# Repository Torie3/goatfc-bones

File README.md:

# 🐐 GoatFC-Bones - Open Source FPV Flight Controller

<div align="left">
  <p>
    <strong>GoatFC-Bones</strong> is a compact, cheap, open-source FPV drone flight controller designed for racing builds without sacrificing performance. It’s ideal for hobbyists who want simple hardware so that they can easily understand what is happening in their quadcopter.
  </p>
</div>

## 🔧 Key Features

- **Voltage Regulation:**
  - 5V and 12V BEC outputs
  - Dual 3.3V LDOs:
    - One dedicated to the IMU for **noise isolation**
    - One for the rest of the system

- **Connectivity:**
  - Micro-USB for configuration
  - 20x20mm standard mounting pattern
  - ESC connector for clean wiring
  - 6-pin HD video system plug

- **Software:**
  - Compatible with [Betaflight](https://betaflight.com/) no official target yet!

- **License & Use:**
  - **Open-source** – build it, modify it, improve it
  - **Non-commercial** – redistribution for sale is **not allowed**
## 🧷 Pinout Diagram

Below is the pinout for the GoatFC-Bones flight controller. Make sure to reference this schematic when wiring your components.

> ⚠️ **Note:** The dedicated 3.3V regulators *are* broken out on the board, but **they are not intended for external use**. If you're curious about their exact location or implementation, please refer to the KiCad design files. Avoid connecting anything to these lines unless you fully understand the design — using them improperly may cause instability or damage.

> 🔌 Always double-check with a multimeter before connecting components!
## 🛠️ Building Your Own GoatFC-Bones

Amazing that you want to build one!

You can order the PCBs from your favorite PCB manufacturer — the Gerber files are available in the folder:  
[Gerber Files Folder](./gerber%20files)

### 📦 Bill of Materials (BOM)

The BOM is provided as an **interactive BOM**, which you can view here:  
[Download and open html file here](./interactive-bom)

The iBOM makes it easy to locate and identify all the required components. Just search for the parts and order them from your preferred distributor.

### 🔧 Assembly Tips

- Solder all components following the iBOM placement guide
- Use **solder paste** and a **hot air station** for best results
- All components are **0402 size** — small, but manageable with some patience
- If you're new to SMD soldering, it's a good idea to practice on a scrap board first!

Good luck, and enjoy flying with your custom GoatFC-Bones FC!

## Flashing Betaflight to GoatFC-Bones

Follow these steps to flash Betaflight firmware to your GoatFC-Bones flight controller:

### Requirements
- A fully assembled GoatFC-Bones FC
- [Betaflight Configurator](https://github.com/betaflight/betaflight-configurator/releases) (latest version) installed on your PC

### Flashing Steps

1. **Build and assemble** your GoatFC-Bones FC.
2. **Install the latest Betaflight Configurator** on your computer.
3. **Enter DFU mode**:
   - Hold down the **boot button** on the FC while plugging in the **Micro-USB** cable.
4. In Betaflight Configurator, your FC should now show up as **DFU Bootloader**.
5. Go to the **Firmware Flasher** tab.
6. Under **Board**, select:  
   **`FOXEERF722V4`** (GoatFC-Bones shares a pinout with the Foxeer Mini V4).
7. Choose your preferred **firmware version** from the dropdown.
8. Click **Load Firmware [Online]**.
9. Then click **Flash Firmware**.
10. Once flashing is complete, the firmware is installed and ready to go! 🎉

### ⚠️ Important: Motor Remapping Required

Because the motor layout on GoatFC-Bones differs from the Foxeer Mini V4, you must **remap the motors** in the CLI:

1. Go to the **CLI** tab
2. In the cli type:
```
resource MOTOR 1 PC08
resource MOTOR 2 PC09
resource MOTOR 3 PA08
resource MOTOR 4 PA09
save
```
4. Now your motors should be in the correct order.
- You only need to do this once — after that, you can **save your configuration as a preset** to reload easily next time.

> 💡 Tip: After remapping, test motor directions in the “Motors” tab and double-check the order before your first flight.

---

## ⚠️ Disclaimer

This project is provided **as-is** without any warranty or guarantee of functionality or safety.

By using the GoatFC-Bones design files, firmware configurations, or build instructions, you acknowledge and agree that:

- You are solely responsible for your own safety and the safety of others.
- You assume all risks associated with the assembly, flashing, and use of this hardware.
- I (the creator) am **not liable** for any damage, injury, loss, or malfunction resulting from the use, misuse, or failure of this project.
- Always follow proper electrical and flight safety practices, and ensure compliance with your local laws and regulations.

> 🚧 Use at your own risk. This is an open-source DIY project intended for educational and recreational purposes (drone racing an amazing hobby!).

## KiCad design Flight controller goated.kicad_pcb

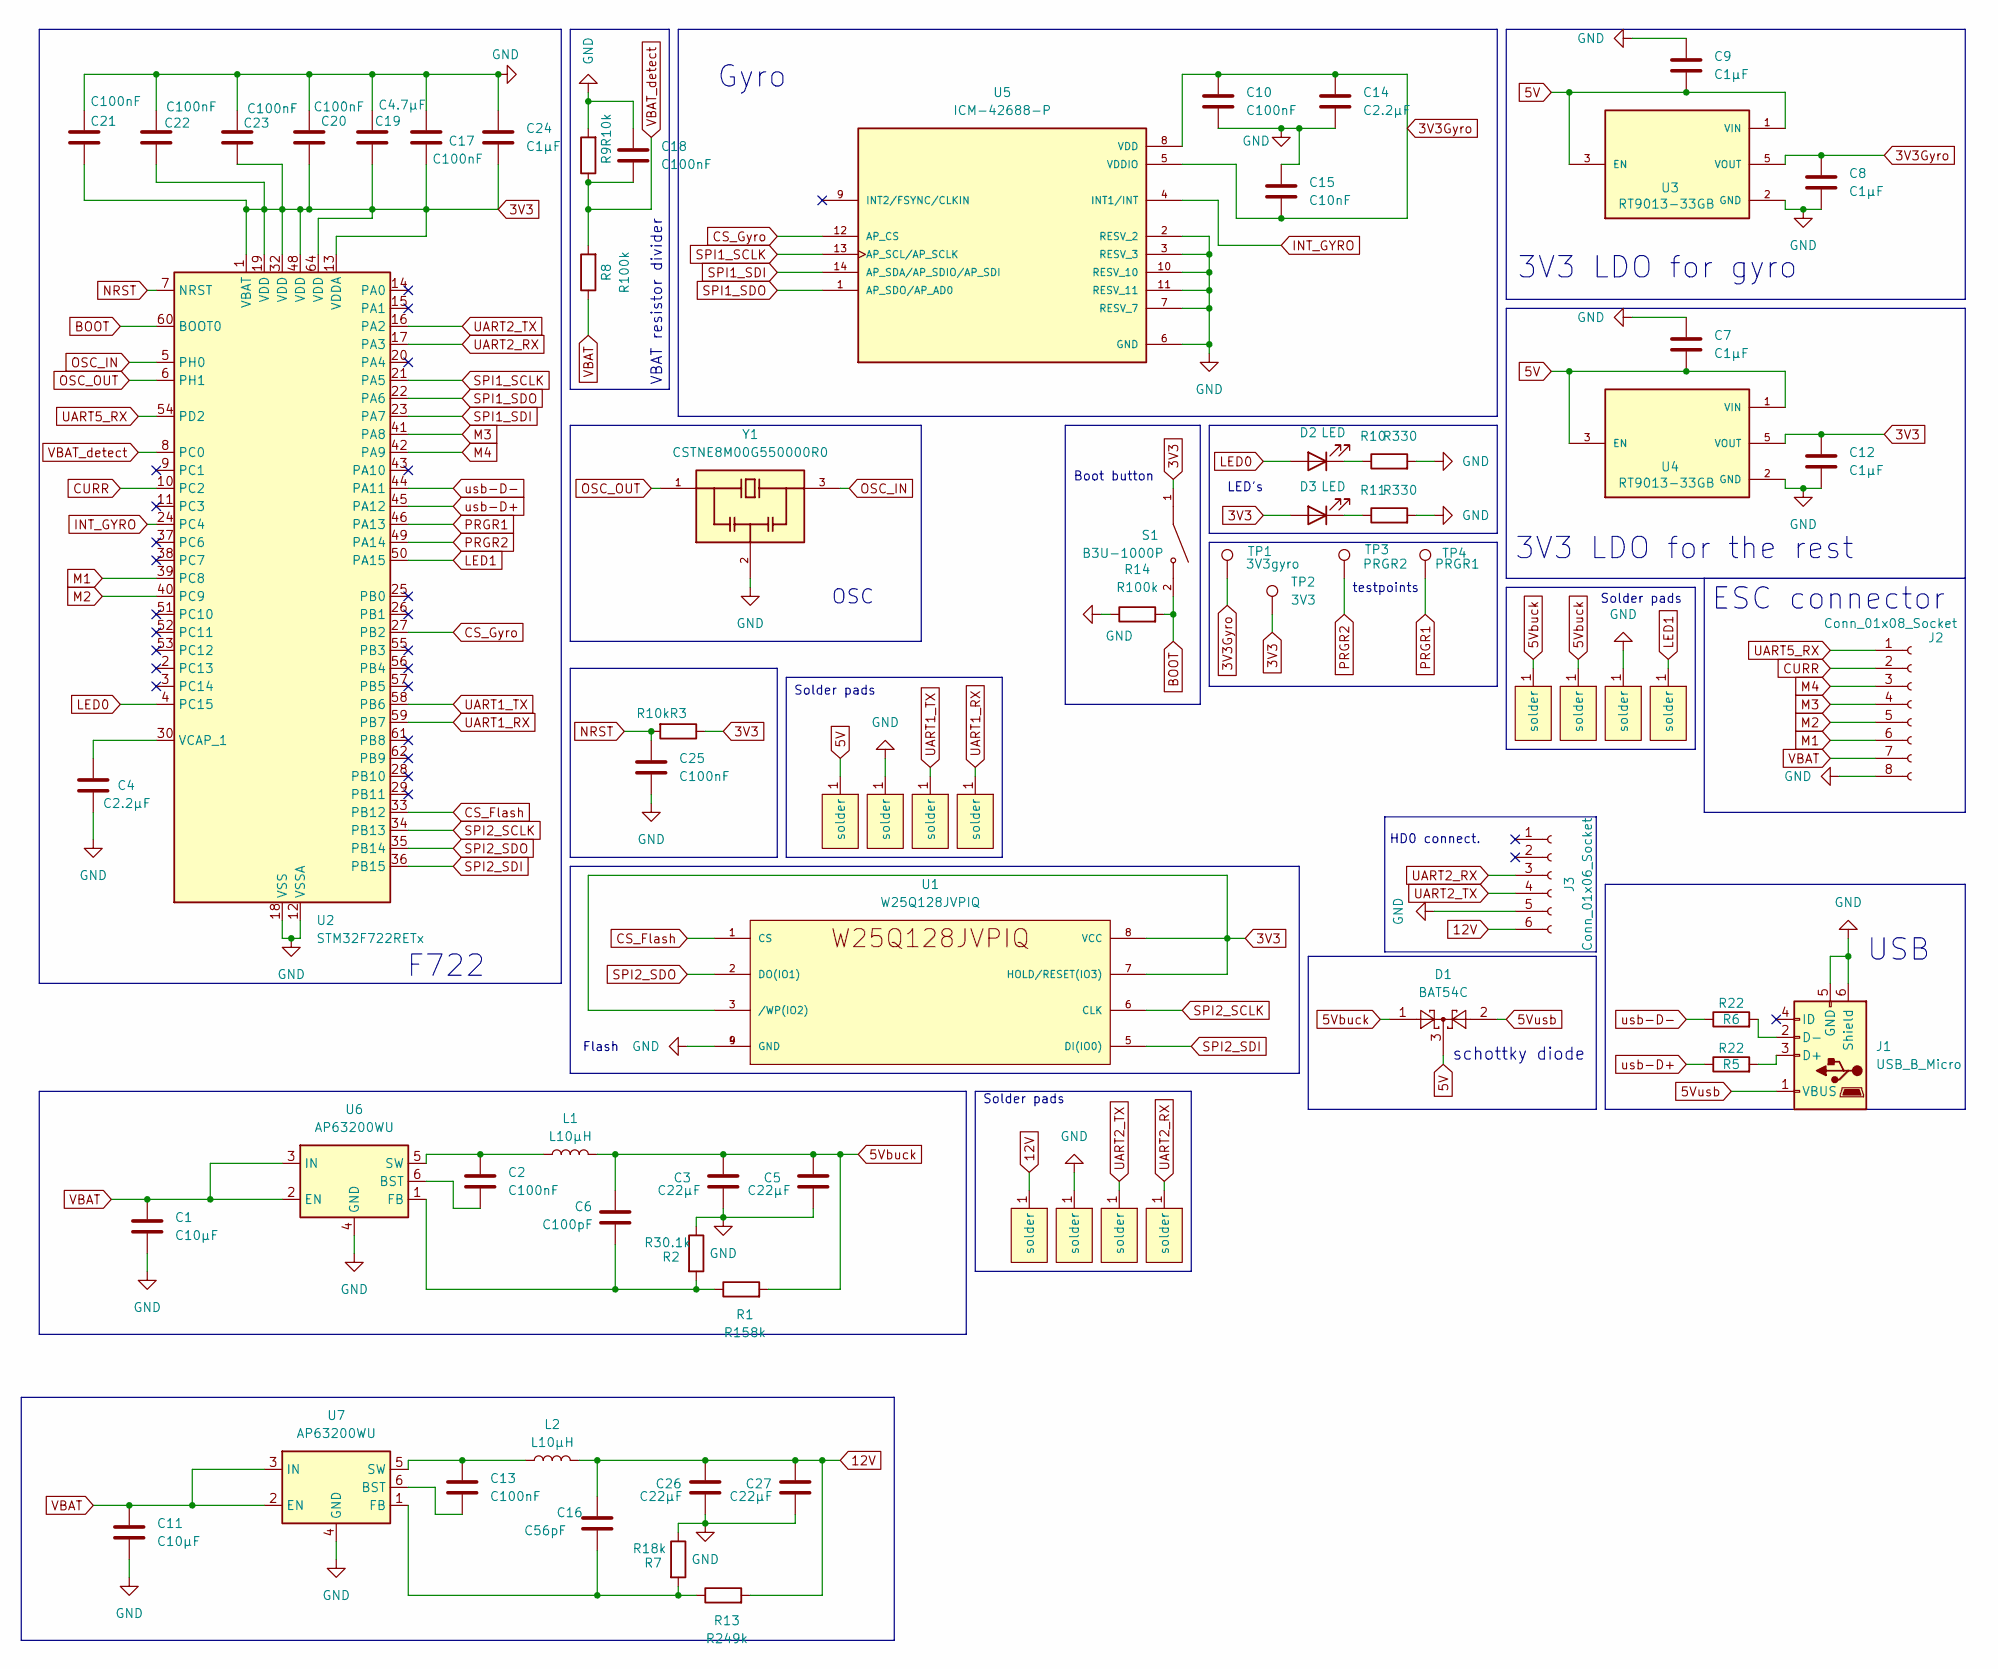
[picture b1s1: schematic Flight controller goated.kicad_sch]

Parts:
C1, C11: C10µF; C_1206_3216Metric
C2, C10, C13, C17, C18, C20, C21, C22, C23, C25: C100nF; C_0402_1005Metric
C3, C5, C26, C27: C22µF; C_0603_1608Metric
C4, C14: C2.2µF; C_0402_1005Metric
C6: C100pF; C_0402_1005Metric
C7, C8, C9, C12, C24: C1µF; C_0402_1005Metric
C15: C10nF; C_0402_1005Metric
C16: C56pF; C_0402_1005Metric
C19: C4.7µF; C_0402_1005Metric
D1: BAT54C; SOT-23
D2: LED; LED_0402_1005Metric
D3: LED; LED_0603_1608Metric
J1: USB_B_Micro; USB_Micro-B_Amphenol_10118194-0001LF_Horizontal
J2: Conn_01x08_Socket; JST_SH_SM08B-SRSS-TB_1x08-1MP_P1.00mm_Horizontal
J3: Conn_01x06_Socket; JST_SH_SM06B-SRSS-TB_1x06-1MP_P1.00mm_Horizontal
L1, L2: L10µH; TECHFUSE SL0420-100M
R1: R158k; R_0603_1608Metric
R2: R30.1k; R_0402_1005Metric
R3, R9: R10k; R_0402_1005Metric
R5, R6: R22; R_0402_1005Metric
R7: R18k; R_0402_1005Metric
R8, R14: R100k; R_0402_1005Metric
R10, R11: R330; R_0402_1005Metric
R13: R249k; R_0603_1608Metric
S1: B3U-1000P; SW_B3U-1000P
S2, S3, S4, S5, S6, S7, S8, S9, S10, S11, S12, S13: solder pad; solder pad small
TP1: 3V3gyro; TestPoint_Pad_D1.0mm
TP2: 3V3; TestPoint_Pad_D1.0mm
TP3: PRGR2; TestPoint_Pad_D1.0mm
TP4: PRGR1; TestPoint_Pad_D1.0mm
U1: W25Q128JVPIQ
U2: STM32F722RETx; LQFP-64_10x10mm_P0.5mm
U3, U4: RT9013-33GB; SOT94P279X129-5N; PARTREV Aprill 2011
U5: ICM-42688-P; PQFN50P300X250X97-14N; PARTREV 1.2
U6, U7: AP63200WU; TSOT-23-6
Y1: CSTNE8M00G550000R0; OSC_CSTNE8M00G550000R0

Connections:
3V3: C12.1, C17.2, C19.2, C20.2, C21.2, C22.2, C23.2, C24.2, D3.2 (A), R3.1, S1.1, TP2.1, U1.3 (/WP(IO2)), U1.7 (HOLD/RESET(IO3)), U1.8 (VCC), U2.1 (VBAT), U2.13 (VDDA), U2.19 (VDD), U2.32 (VDD), U2.48 (VDD), U2.64 (VDD), U4.5 (VOUT)
3V3Gyro: C8.1, C10.1, C14.1, C15.2, TP1.1, U3.5 (VOUT), U5.5 (VDDIO), U5.8 (VDD)
5V: C7.2, C9.2, D1.3, S6.1 (solder), U3.1 (VIN), U3.3 (EN), U4.1 (VIN), U4.3 (EN)
5Vbuck: C3.1, C5.1, C6.2, D1.1, L1.2, R1.2, S10.1 (solder), S13.1 (solder)
5Vusb: D1.2, J1.1 (VBUS)
12V: C16.2, C26.1, C27.1, J3.6, L2.2, R13.2, S2.1 (solder)
BOOT: R14.2, S1.2, U2.60 (BOOT0)
CS_Flash: U1.1 (CS), U2.33 (PB12)
CS_Gyro: U2.27 (PB2), U5.12 (AP_CS)
CURR: J2.2, U2.10 (PC2)
GND: C1.2, C3.2, C4.2, C5.2, C7.1, C8.2, C9.1, C10.2, C11.2, C12.2, C14.2, C15.1, C17.1, C18.1, C19.1, C20.1, C21.1, C22.1, C23.1, C24.1, C25.2, C26.2, C27.2, J1.5 (GND), J1.6 (Shield), J2.8, J3.5, R2.1, R7.1, R9.2, R10.2, R11.2, R14.1, S3.1 (solder), S7.1 (solder), S11.1 (solder), U1.4 (GND), U1.9 (GND), U2.12 (VSSA), U2.18 (VSS), U2.31 (VSS), U2.47 (VSS), U2.63 (VSS), U3.2 (GND), U4.2 (GND), U5.2 (RESV_2), U5.3 (RESV_3), U5.6 (GND), U5.7 (RESV_7), U5.10 (RESV_10), U5.11 (RESV_11), U6.4 (GND), U7.4 (GND), Y1.2
INT_GYRO: U2.24 (PC4), U5.4 (INT1/INT)
LED0: D2.2 (A), U2.4 (PC15)
LED1: S12.1 (solder), U2.50 (PA15)
M1: J2.6, U2.39 (PC8)
M2: J2.5, U2.40 (PC9)
M3: J2.4, U2.41 (PA8)
M4: J2.3, U2.42 (PA9)
NRST: C25.1, R3.2, U2.7 (NRST)
unnamed: D2.1 (K), R10.1
unnamed: D3.1 (K), R11.1
unnamed: J1.3 (D+), R5.2
unnamed: J1.2 (D-), R6.2
unnamed: C4.1, U2.30 (VCAP_1)
unnamed: C2.2, U6.6 (BST)
unnamed: C6.1, R1.1, R2.2, U6.1 (FB)
unnamed: C2.1, L1.1, U6.5 (SW)
unnamed: C13.2, U7.6 (BST)
unnamed: C16.1, R7.2, R13.1, U7.1 (FB)
unnamed: C13.1, L2.1, U7.5 (SW)
OSC_IN: U2.5 (PH0), Y1.3
OSC_OUT: U2.6 (PH1), Y1.1
PRGR1: TP4.1, U2.46 (PA13)
PRGR2: TP3.1, U2.49 (PA14)
SPI1_SCLK: U2.21 (PA5), U5.13 (AP_SCL/AP_SCLK)
SPI1_SDI: U2.23 (PA7), U5.14 (AP_SDA/AP_SDIO/AP_SDI)
SPI1_SDO: U2.22 (PA6), U5.1 (AP_SDO/AP_AD0)
SPI2_SCLK: U1.6 (CLK), U2.34 (PB13)
SPI2_SDI: U1.5 (DI(IO0)), U2.36 (PB15)
SPI2_SDO: U1.2 (DO(IO1)), U2.35 (PB14)
UART1_RX: S9.1 (solder), U2.59 (PB7)
UART1_TX: S8.1 (solder), U2.58 (PB6)
UART2_RX: J3.3, S5.1 (solder), U2.17 (PA3)
UART2_TX: J3.4, S4.1 (solder), U2.16 (PA2)
UART5_RX: J2.1, U2.54 (PD2)
VBAT: C1.1, C11.1, J2.7, R8.1, U6.2 (EN), U6.3 (IN), U7.2 (EN), U7.3 (IN)
VBAT_detect: C18.2, R8.2, R9.1, U2.8 (PC0)
usb-D+: R5.1, U2.45 (PA12)
usb-D-: R6.1, U2.44 (PA11)

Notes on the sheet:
Solder pads
F722
schottky diode
Gyro
3V3 LDO for the rest
VBAT resistor divider
Boot button
HD0 connect.
USB
testpoints
Flash
OSC
LED's
ESC connector
3V3 LDO for gyro

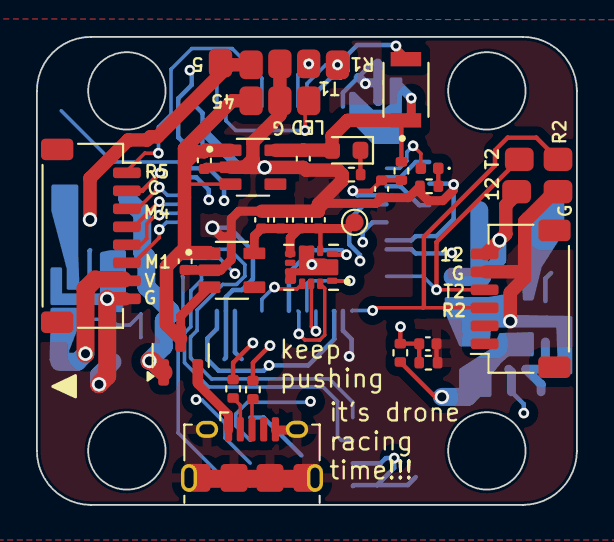
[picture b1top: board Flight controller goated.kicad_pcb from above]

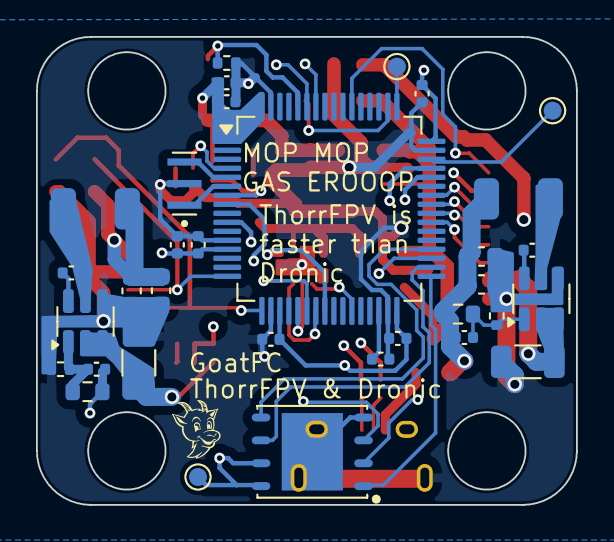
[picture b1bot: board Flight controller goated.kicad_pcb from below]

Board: 4 copper layers, 30.0 x 26.0 mm, 72 parts (33 on the bottom side), 49 nets.

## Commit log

2025-06-23 add everything lol
2025-06-23 add pictures
2025-06-23 Create LICENSE
2025-06-23 added pinout picture
2025-06-23 change folder name
2025-06-23 add picture of IBOM
2025-06-24 added RT9013-33GB reference chip
